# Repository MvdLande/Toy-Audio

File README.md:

# Toy-Audio
Simple WAV player for toys

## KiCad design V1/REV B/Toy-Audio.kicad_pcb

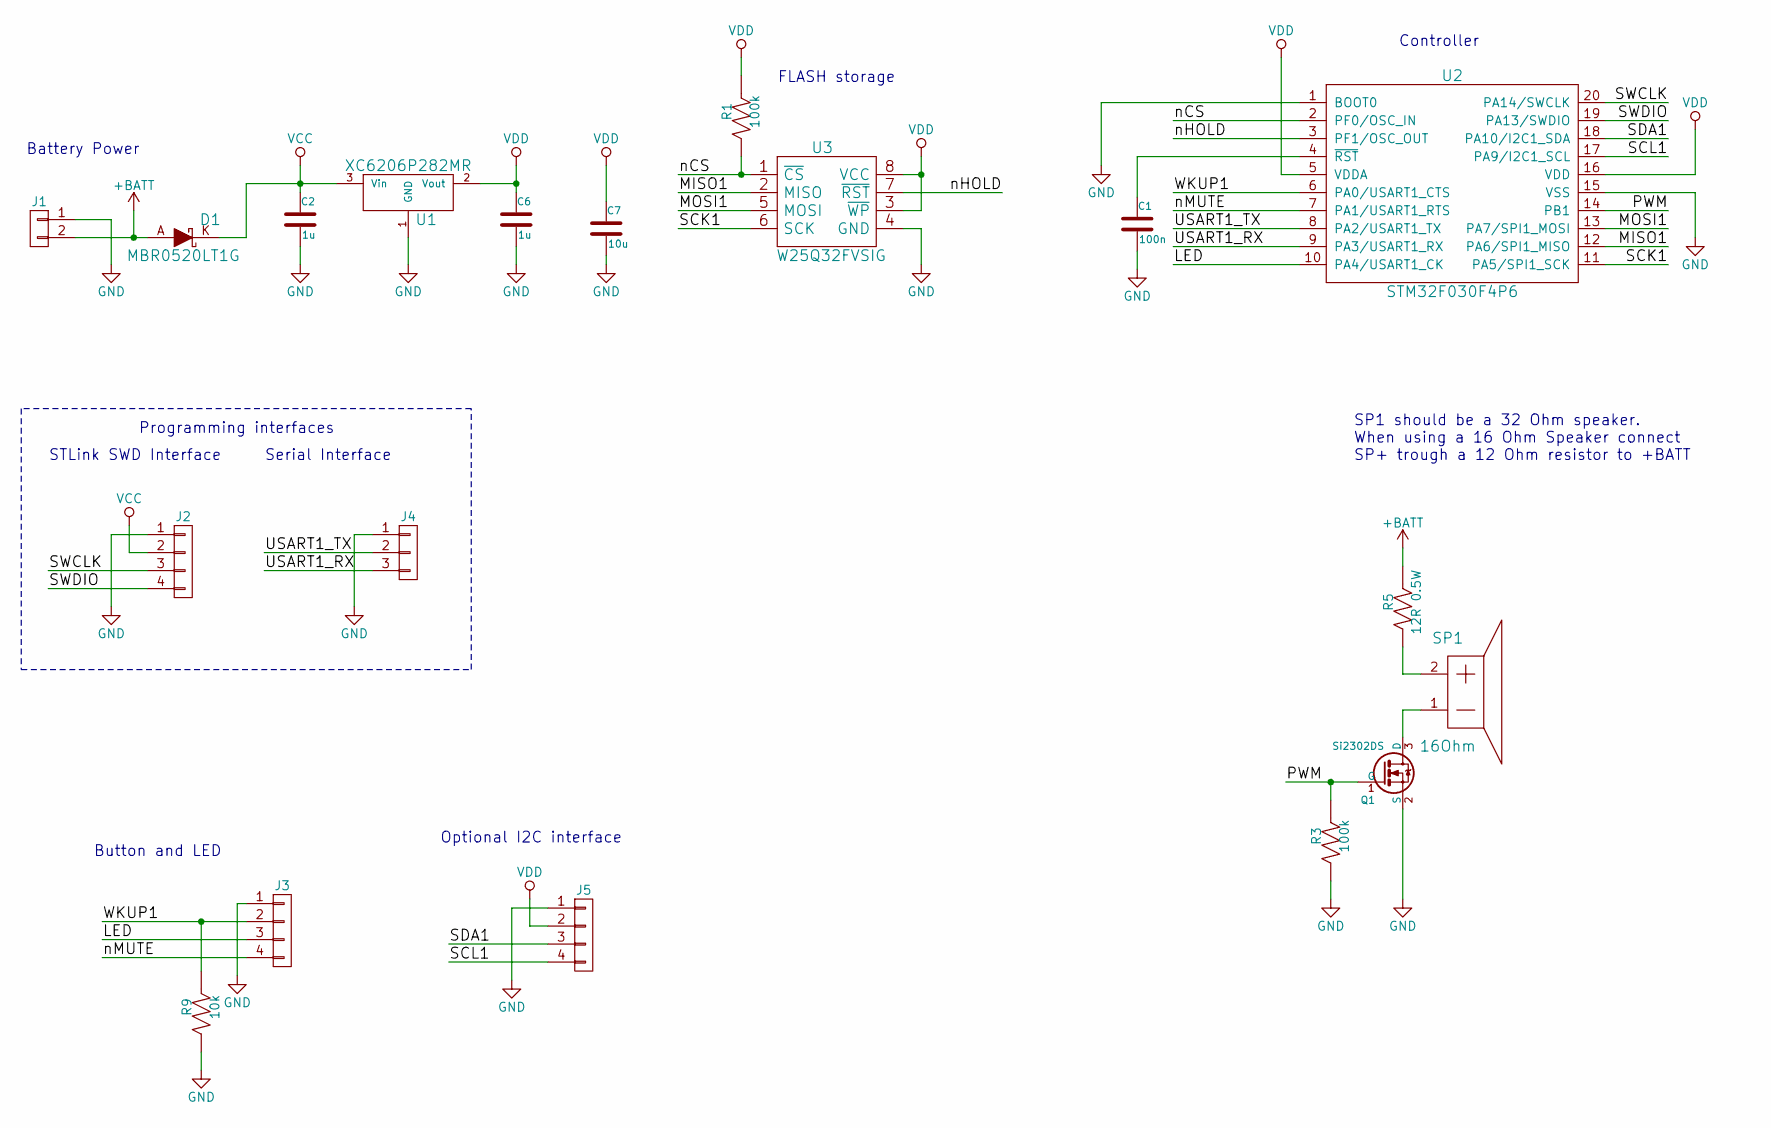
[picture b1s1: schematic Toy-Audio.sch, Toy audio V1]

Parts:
C1: 100n; C0603
C2, C6: 1u; C0603
C7: 10u; C0603
D1: MBR0520LT1G; SOD-123
J1: CONN_01X02; HDR_01x02_RM2.54
J2: CONN_01X04; HDR-01X4-RM2
J3, J5: CONN_01X04; HDR_01x04_RM2.54
J4: CONN_01X03; HDR-01X3-RM2
Q1: Si2302DS; SOT23
R1, R3: 100k; R0603
R5: 12R 0.5W; R0603
R9: 10k; R0603
SP1: 16Ohm; HDR_01x02_RM2.54
U1: XC6206P282MR; SOT23
U2: STM32F030F4P6; TSSOP20
U3: W25Q32FVSIG; SOIC-8-208mil

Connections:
+BATT: D1.A, J1.2, R5.2
/LED: J3.3, U2.10 (PA4/USART1_CK)
/MISO1: U2.12 (PA6/SPI1_MISO), U3.2 (MISO)
/MOSI1: U2.13 (PA7/SPI1_MOSI), U3.5 (MOSI)
/PWM: Q1.1 (G), R3.2, U2.14 (PB1)
/SCK1: U2.11 (PA5/SPI1_SCK), U3.6 (SCK)
/SCL1: J5.4, U2.17 (PA9/I2C1_SCL)
/SDA1: J5.3, U2.18 (PA10/I2C1_SDA)
/SWCLK: J2.3, U2.20 (PA14/SWCLK)
/SWDIO: J2.4, U2.19 (PA13/SWDIO)
/USART1_RX: J4.3, U2.9 (PA3/USART1_RX)
/USART1_TX: J4.2, U2.8 (PA2/USART1_TX)
/WKUP1: J3.2, R9.2, U2.6 (PA0/USART1_CTS)
/nCS: R1.1, U2.2 (PF0/OSC_IN), U3.1 (~CS)
/nHOLD: U2.3 (PF1/OSC_OUT), U3.7 (~RST)
/nMUTE: J3.4, U2.7 (PA1/USART1_RTS)
GND: C1.2, C2.2, C6.2, C7.2, J1.1, J2.1, J3.1, J4.1, J5.1, Q1.2 (S), R3.1, R9.1, U1.1 (GND), U2.1 (BOOT0), U2.15 (VSS), U3.4 (GND)
unnamed: C1.1, U2.4 (~RST)
unnamed: Q1.3 (D), SP1.1
unnamed: R5.1, SP1.2
VCC: C2.1, D1.K, J2.2, U1.3 (Vin)
VDD: C6.1, C7.1, J5.2, R1.2, U1.2 (Vout), U2.5 (VDDA), U2.16 (VDD), U3.3 (~WP), U3.8 (VCC)

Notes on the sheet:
STLink SWD Interface
Battery Power
Serial Interface
Button and LED
Optional I2C interface
Programming interfaces
FLASH storage
Controller
SP1 should be a 32 Ohm speaker. When using a 16 Ohm Speaker connect SP+ trough a 12 Ohm resistor to +BATT

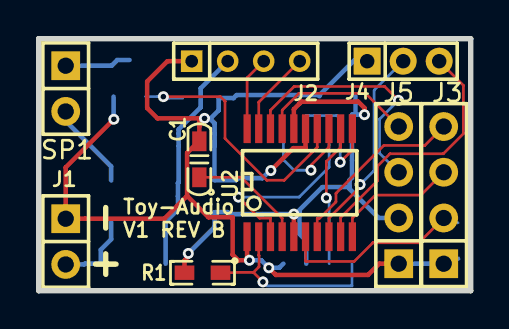
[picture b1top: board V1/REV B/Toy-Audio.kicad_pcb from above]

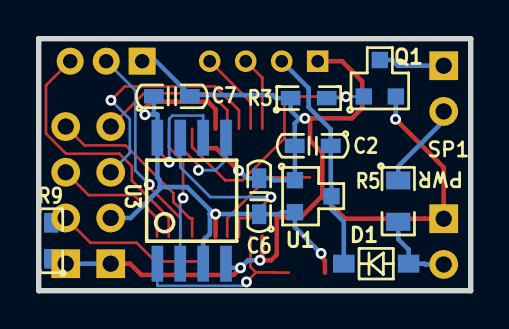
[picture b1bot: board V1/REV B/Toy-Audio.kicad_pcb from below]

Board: 2 copper layers, 24.0 x 14.0 mm, 19 parts (10 on the bottom side), 22 nets.

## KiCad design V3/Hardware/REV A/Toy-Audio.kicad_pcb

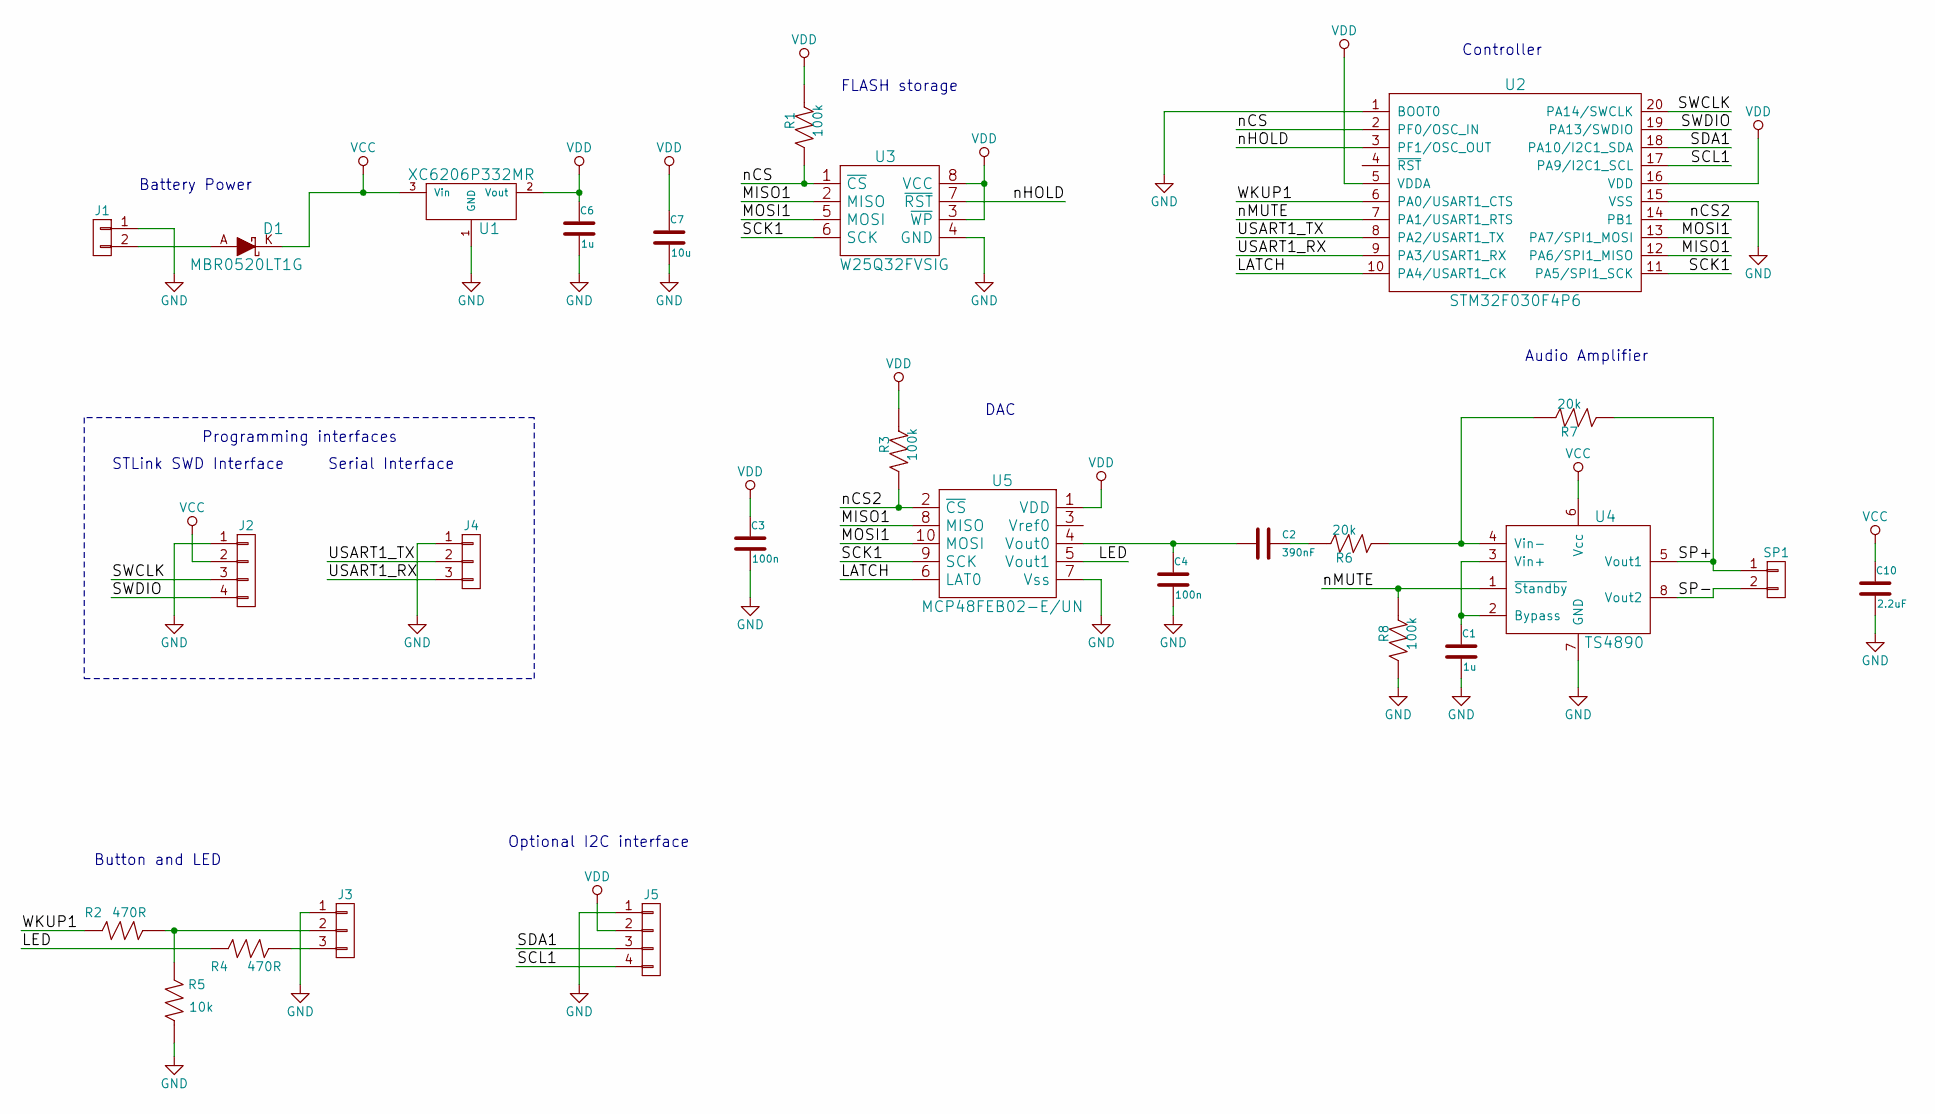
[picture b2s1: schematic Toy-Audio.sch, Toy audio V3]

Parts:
C1, C6: 1u; C0603
C2: 390nF; C0603
C3, C4: 100n; C0603
C7: 10u; C0603
C10: 2.2uF; C0603
D1: MBR0520LT1G; SOD-123
J1: CONN_01X02; HDR_01x02_RM2.54
J2: CONN_01X04; HDR-01X4-RM2
J3, J4: CONN_01X03; HDR_01x03_RM2.54
J5: CONN_01X04; HDR_01x04_RM2.54
R1, R3, R8: 100k; R0603
R2, R4: 470R; R0603
R5: 10k; R0603
R6, R7: 20k; R0603
SP1: CONN_01X02; HDR_01x02_RM2.54
U1: XC6206P332MR; SOT23
U2: STM32F030F4P6; TSSOP20
U3: W25Q32FVSIG; SOIC-8-208mil
U4: TS4890; MSOP8
U5: MCP48FEB02-E/UN; MSOP10

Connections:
/LATCH: U2.10 (PA4/USART1_CK), U5.6 (LAT0)
/LED: R4.1, U5.5 (Vout1)
/MISO1: U2.12 (PA6/SPI1_MISO), U3.2 (MISO), U5.8 (MISO)
/MOSI1: U2.13 (PA7/SPI1_MOSI), U3.5 (MOSI), U5.10 (MOSI)
/SCK1: U2.11 (PA5/SPI1_SCK), U3.6 (SCK), U5.9 (SCK)
/SCL1: J5.4, U2.17 (PA9/I2C1_SCL)
/SDA1: J5.3, U2.18 (PA10/I2C1_SDA)
/SP+: R7.1, SP1.1, U4.5 (Vout1)
/SP-: SP1.2, U4.8 (Vout2)
/SWCLK: J2.3, U2.20 (PA14/SWCLK)
/SWDIO: J2.4, U2.19 (PA13/SWDIO)
/USART1_RX: J4.3, U2.9 (PA3/USART1_RX)
/USART1_TX: J4.2, U2.8 (PA2/USART1_TX)
/WKUP1: R2.1, U2.6 (PA0/USART1_CTS)
/nCS: R1.1, U2.2 (PF0/OSC_IN), U3.1 (~CS)
/nCS2: R3.1, U2.14 (PB1), U5.2 (~CS)
/nHOLD: U2.3 (PF1/OSC_OUT), U3.7 (~RST)
/nMUTE: R8.2, U2.7 (PA1/USART1_RTS), U4.1 (~Standby)
GND: C1.2, C3.2, C4.2, C6.2, C7.2, C10.2, J1.1, J2.1, J3.1, J4.1, J5.1, R5.2, R8.1, U1.1 (GND), U2.1 (BOOT0), U2.15 (VSS), U3.4 (GND), U4.7 (GND), U5.7 (Vss)
unnamed: C1.1, U4.2 (Bypass), U4.3 (Vin+)
unnamed: C2.1, R6.2
unnamed: C2.2, C4.1, U5.4 (Vout0)
unnamed: D1.A, J1.2
unnamed: J3.2, R2.2, R5.1
unnamed: J3.3, R4.2
unnamed: R6.1, R7.2, U4.4 (Vin-)
VCC: C10.1, D1.K, J2.2, U1.3 (Vin), U4.6 (Vcc)
VDD: C3.1, C6.1, C7.1, J5.2, R1.2, R3.2, U1.2 (Vout), U2.5 (VDDA), U2.16 (VDD), U3.3 (~WP), U3.8 (VCC), U5.1 (VDD)

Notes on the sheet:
STLink SWD Interface
Battery Power
Serial Interface
Button and LED
Optional I2C interface
Programming interfaces
FLASH storage
Audio Amplifier
Controller
DAC

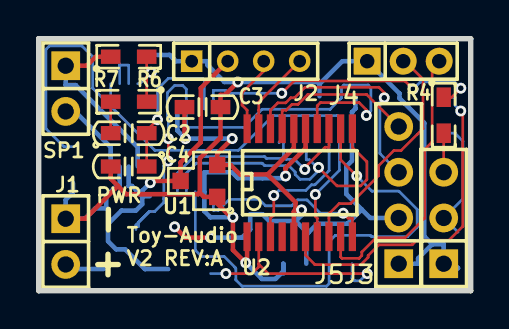
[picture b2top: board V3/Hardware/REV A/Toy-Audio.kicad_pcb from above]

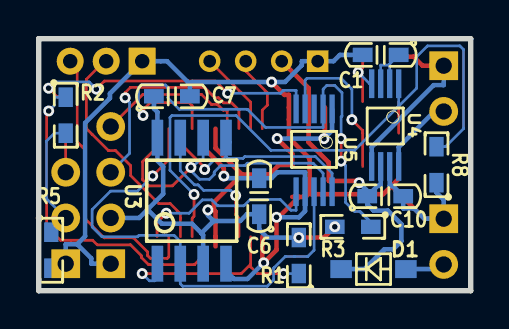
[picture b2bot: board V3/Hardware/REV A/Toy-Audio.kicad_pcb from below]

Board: 2 copper layers, 24.0 x 14.0 mm, 27 parts (13 on the bottom side), 28 nets.

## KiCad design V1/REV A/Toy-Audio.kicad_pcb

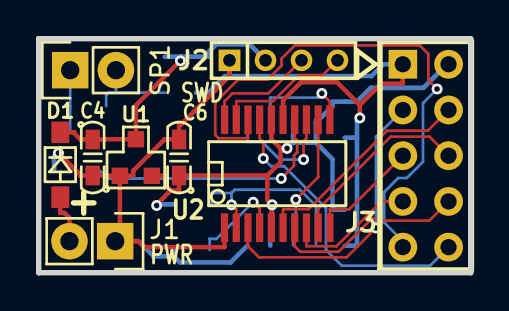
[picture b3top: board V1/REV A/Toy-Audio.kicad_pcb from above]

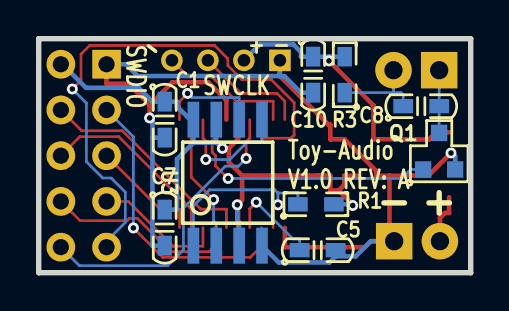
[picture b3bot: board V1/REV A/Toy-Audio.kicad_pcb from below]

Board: 2 copper layers, 24.0 x 13.0 mm, 18 parts (9 on the bottom side), 22 nets.

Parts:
C1, C4, C7: 10u; C0603
C5: 100n; C0603
C6: 1u; C0603
C8: 22nF; C0603
C10: 10uF; C0603
D1: MBR0520LT1G; SOD-123
J1: CONN_2; Pin_Header_Straight_1x02
J2: CONN_01X04; HDR-01X4-RM2
J3: CONN_01X10; HDR_5x2
Q1: Si2302DS; SOT23
R1: 100k; R0603
R3: 1R; R0603
SP1: 8Ohm; Pin_Header_Straight_1x02
U1: XC6206P332MR; SOT23
U2: STM32F030Fx; TSSOP20
U3: W25Q128FVSIG; SOIC-8-208mil

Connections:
/MISO1: U2.12, U3.2
/MOSI1: U2.13, U3.5
/PWM: Q1.1, U2.14
/SCK1: U2.11, U3.6
/SCL1: J3.10, U2.17
/SDA1: J3.9, U2.18
/SWCLK: J2.3, U2.20
/SWDIO: J2.4, U2.19
/UART2_EN: J3.3, U2.3
/USART2_CK: J3.5, U2.10
/USART2_CTS: J3.4, U2.6
/USART2_RTS: J3.8, U2.7
/USART2_RX: J3.6, U2.9
/USART2_TX: J3.7, U2.8
/~CS-FL: R1.1, U2.2, U3.1
GND: C1.2, C4.2, C5.2, C6.2, C7.2, C10.2, J1.1, J2.1, J3.1, Q1.2, U1.1, U2.1, U2.15, U3.4
unnamed: C5.1, U2.4
unnamed: C8.1, R3.1, SP1.2
unnamed: C8.2, Q1.3, SP1.1
unnamed: D1.A, J1.2
VCC: C4.1, C10.1, D1.C, J2.2, R3.2, U1.3
VDD: C1.1, C6.1, C7.1, J3.2, R1.2, U1.2, U2.5, U2.16, U3.3, U3.7, U3.8

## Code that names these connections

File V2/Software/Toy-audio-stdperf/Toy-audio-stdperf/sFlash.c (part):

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	RCC_AHBPeriphClockCmd(RCC_AHBPeriph_GPIOF, ENABLE);
  

	// SPI1 Master initialization, SCK -> PA5
	GPIO_StructInit(&GPIO_InitStructure);
	GPIO_InitStructure.GPIO_Pin = GPIO_Pin_5;
	GPIO_InitStructure.GPIO_Mode = GPIO_Mode_OUT;
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	GPIO_InitStructure.GPIO_Speed = GPIO_Speed_50MHz;
	GPIO_Init(GPIOA, &GPIO_InitStructure);

	// SPI1 MASTER initialization, MISO -> PA6
	GPIO_StructInit(&GPIO_InitStructure);
	GPIO_InitStructure.GPIO_Pin = GPIO_Pin_6;
	GPIO_InitStructure.GPIO_Mode = GPIO_Mode_IN;
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	GPIO_InitStructure.GPIO_Speed = GPIO_Speed_50MHz;
	GPIO_Init(GPIOA, &GPIO_InitStructure);

	// SPI1 Master initialization, MOSI -> PA7
	GPIO_StructInit(&GPIO_InitStructure);
	GPIO_InitStructure.GPIO_Pin = GPIO_Pin_7;
	GPIO_InitStructure.GPIO_Mode = GPIO_Mode_OUT;
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	GPIO_InitStructure.GPIO_Speed = GPIO_Speed_50MHz;
	GPIO_Init(GPIOA, &GPIO_InitStructure);
	
	// CS -> PF0
	GPIO_StructInit(&GPIO_InitStructure);
	GPIO_InitStructure.GPIO_Pin = GPIO_Pin_0; // nCS pin
	GPIO_InitStructure.GPIO_Mode = GPIO_Mode_OUT;
	GPIO_InitStructure.GPIO_OType = GPIO_OType_PP; 
	GPIO_InitStructure.GPIO_PuPd = GPIO_PuPd_NOPULL;
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	RCC_AHBPeriphClockCmd(RCC_AHBPeriph_GPIOF, ENABLE);
  

	// SPI1 Master initialization, SCK -> PA5
	GPIO_StructInit(&GPIO_InitStructure);
	GPIO_InitStructure.GPIO_Pin = GPIO_Pin_5;
	GPIO_InitStructure.GPIO_Mode = GPIO_Mode_AF;
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	GPIO_InitStructure.GPIO_Speed = GPIO_Speed_50MHz;
	GPIO_Init(GPIOA, &GPIO_InitStructure);

	// SPI1 MASTER initialization, MISO -> PA6
	GPIO_StructInit(&GPIO_InitStructure);
	GPIO_InitStructure.GPIO_Pin = GPIO_Pin_6;
	GPIO_InitStructure.GPIO_Mode = GPIO_Mode_AF;
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	GPIO_InitStructure.GPIO_Speed = GPIO_Speed_50MHz;
	GPIO_Init(GPIOA, &GPIO_InitStructure);

	// SPI1 Master initialization, MOSI -> PA7
	GPIO_StructInit(&GPIO_InitStructure);
	GPIO_InitStructure.GPIO_Pin = GPIO_Pin_7;
	GPIO_InitStructure.GPIO_Mode = GPIO_Mode_AF;
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	GPIO_InitStructure.GPIO_Speed = GPIO_Speed_50MHz;
	GPIO_Init(GPIOA, &GPIO_InitStructure);
	
		// SPI1 Master initialization, SCK -> PA5
	GPIO_PinAFConfig(GPIOA, GPIO_PinSource5, GPIO_AF_0); //SPI1
	// SPI1 MASTER initialization, MISO -> PA6
	GPIO_PinAFConfig(GPIOA, GPIO_PinSource6, GPIO_AF_0); //SPI1
	// SPI1 Master initialization, MOSI -> PA7
	GPIO_PinAFConfig(GPIOA, GPIO_PinSource7, GPIO_AF_0); //SPI1
	
	// CS -> PF0
	GPIO_StructInit(&GPIO_InitStructure);
	GPIO_InitStructure.GPIO_Pin = GPIO_Pin_0; // nCS pin
	GPIO_InitStructure.GPIO_Mode = GPIO_Mode_OUT;
	GPIO_InitStructure.GPIO_OType = GPIO_OType_PP; 
	GPIO_InitStructure.GPIO_PuPd = GPIO_PuPd_NOPULL;
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
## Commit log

2015-12-15 First commit with hardware files
2015-12-15 New source files
2015-12-15 Changed Toy-Audio.sch HW V2 REV A low Pass filter (removed voltage divider) to increase the speaker sound volume
2015-12-15 Added pdf version of the schematic
2015-12-15 Now really include the schematic
2015-12-15 Added Toy-Audio V2 REV A Hand soldering guide
2015-12-16 Modified PCB layout, improved hand solderability.
2015-12-20 Added Standby mode to software V1. Modified hardware to support Standby (add pull up/down resistors) todo hardware V3
2015-12-20 Updated HW V3 schematic and all pdf files.
2015-12-20 Fixed stop button
2015-12-21 Improved Wake-up pin stability WKUP1. modiefied schematic files. Software V1 is compatible with hardware V2
2015-12-22 Added support for SPI FLASH power down function
2015-12-23 added resistor between Speaker + and Vbat to improve stability during playback. (HW V1)
2015-12-23 Added V1 HW REV B
2015-12-23 Added V1 REV B schematic as PDF
2016-01-07 Minimized HW REV A, merged programming Terminal menu into main code. the menu is entered when data is received on the serial interface.
2016-02-07 Modified/added documentation HW V1. changed SPI flash write function to wait for data transmision complete flag.

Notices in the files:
V2/Software/Toy-audio-stdperf/Toy-audio-stdperf/sFlash.c:
© COPYRIGHT 2011 STMicroelectronics
